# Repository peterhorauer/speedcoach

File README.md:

# speedcoach

A rowing speedcoach that measures speed and acceleration and displays them on a Graphic-LCD.

*Parts*

- Microcontroller STM32
- external memory
- GPS module
- Accelerometer
- Bluetooth module
- Graphic LCD
- Buttons

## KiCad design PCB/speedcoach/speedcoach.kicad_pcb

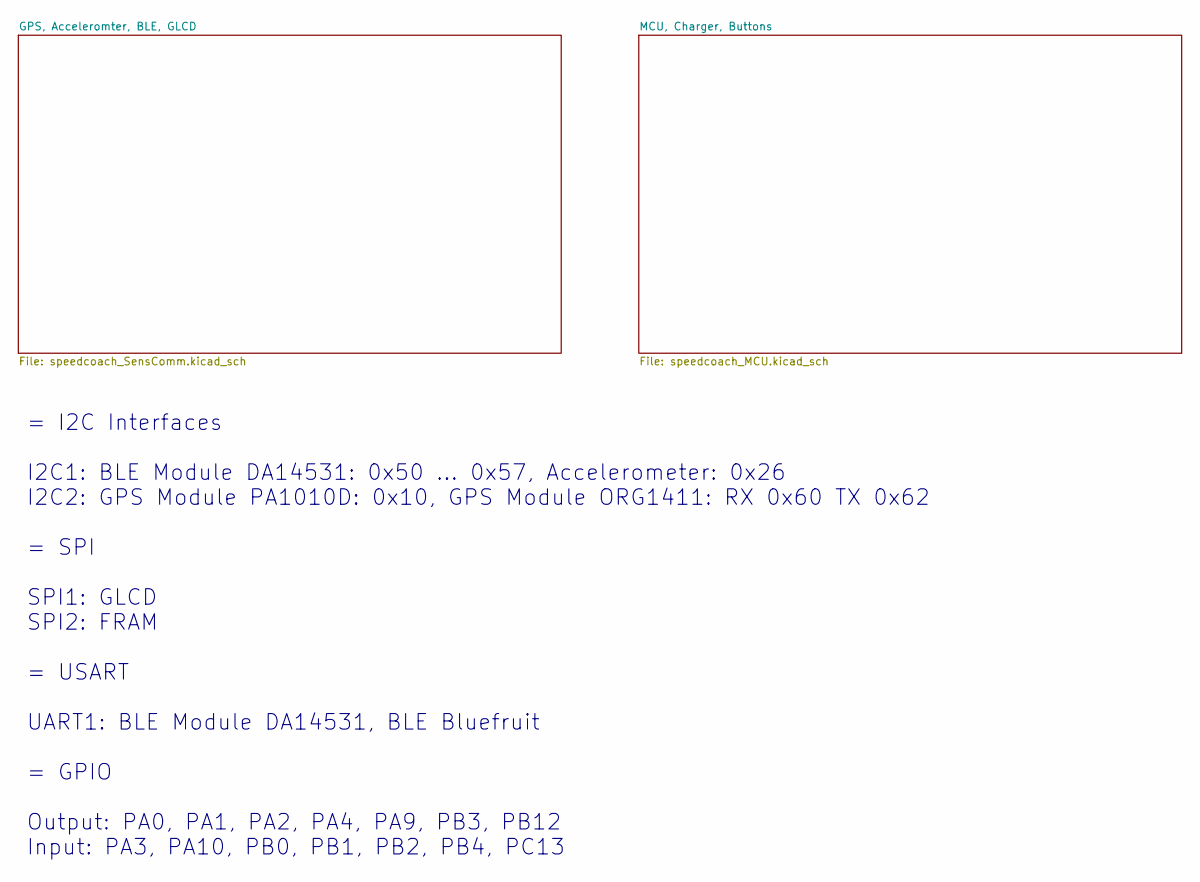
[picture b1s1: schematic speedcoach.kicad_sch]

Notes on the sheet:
= I2C Interfaces I2C1: BLE Module DA14531: 0x50 ... 0x57, Accelerometer: 0x26 I2C2: GPS Module PA1010D: 0x10, GPS Module ORG1411: RX 0x60 TX 0x62 = SPI SPI1: GLCD SPI2: FRAM = USART UART1: BLE Module DA14531, BLE Bluefruit = GPIO Output: PA0, PA1, PA2, PA4, PA9, PB3, PB12 Input: PA3, PA10, PB0, PB1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

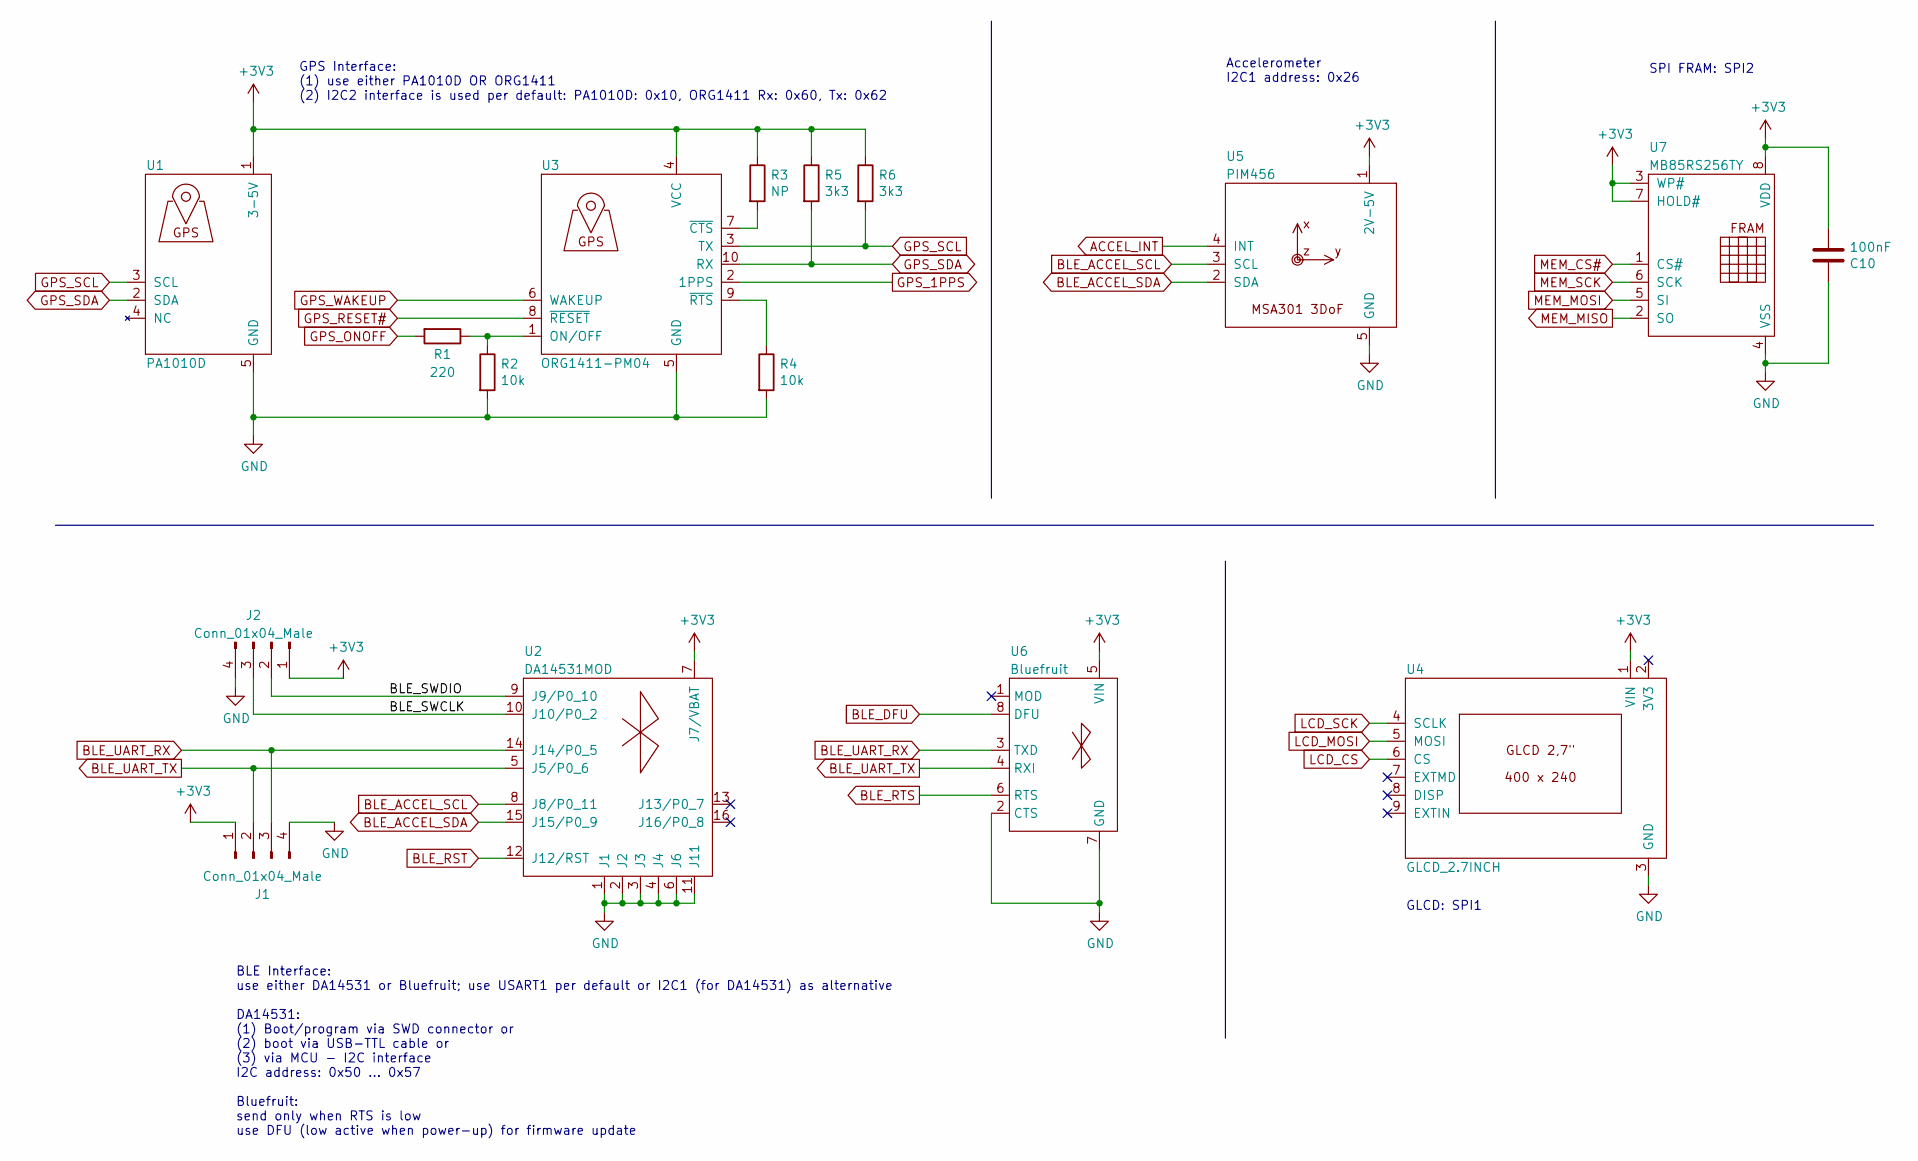
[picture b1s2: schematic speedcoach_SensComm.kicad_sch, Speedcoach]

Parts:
C10: 100nF; C_0805_2012Metric
J1, J2: Conn_01x04_Male; PinHeader_1x04_P2.54mm_Vertical
R1: 220; R_0805_2012Metric
R2, R4: 10k; R_0805_2012Metric
R3: NP; R_0805_2012Metric
R5, R6: 3k3; R_0805_2012Metric
U1: PA1010D; PA1010D_WH
U2: DA14531MOD; DA14531MOD-00F01002
U3: ORG1411-PM04; ORG1411
U4: GLCD_2.7INCH; SHARP_DISPLAY_400x240
U5: PIM456; PIM456_WH
U6: Bluefruit; Bluefruit_WH
U7: MB85RS256TY; SOP-8_3.9x4.9mm_P1.27mm

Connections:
+3V3: C10.1, J1.1, J2.1, R3.1, R5.1, R6.1, U1.1 (3-5V), U2.7 (J7/VBAT), U3.4 (VCC), U4.1 (VIN), U5.1 (2V-5V), U6.5 (VIN), U7.3 (WP#), U7.7 (HOLD#), U7.8 (VDD); also elsewhere on the board
/GPS, Acceleromter, BLE, GLCD/BLE_SWCLK: J2.3, U2.10 (J10/P0_2)
/GPS, Acceleromter, BLE, GLCD/BLE_SWDIO: J2.2, U2.9 (J9/P0_10)
ACCEL_INT: U5.4 (INT); also elsewhere on the board
BLE_ACCEL_SCL: U2.8 (J8/P0_11), U5.3 (SCL); also elsewhere on the board
BLE_ACCEL_SDA: U2.15 (J15/P0_9), U5.2 (SDA); also elsewhere on the board
BLE_DFU: U6.8 (DFU); also elsewhere on the board
BLE_RST: U2.12 (J12/RST); also elsewhere on the board
BLE_RTS: U6.6 (RTS); also elsewhere on the board
BLE_UART_RX: J1.3, U2.14 (J14/P0_5), U6.3 (TXD); also elsewhere on the board
BLE_UART_TX: J1.2, U2.5 (J5/P0_6), U6.4 (RXI); also elsewhere on the board
GND: C10.2, J1.4, J2.4, R2.2, R4.2, U1.5 (GND), U2.1 (J1), U2.2 (J2), U2.3 (J3), U2.4 (J4), U2.6 (J6), U2.11 (J11), U3.5 (GND), U4.3 (GND), U5.5 (GND), U6.2 (CTS), U6.7 (GND), U7.4 (VSS); also elsewhere on the board
GPS_1PPS: U3.2 (1PPS); also elsewhere on the board
GPS_ONOFF: R1.2; also elsewhere on the board
GPS_RESET#: U3.8 (~RESET); also elsewhere on the board
GPS_SCL: R6.2, U1.3 (SCL), U3.3 (TX); also elsewhere on the board
GPS_SDA: R5.2, U1.2 (SDA), U3.10 (RX); also elsewhere on the board
GPS_WAKEUP: U3.6 (WAKEUP); also elsewhere on the board
LCD_CS: U4.6 (CS); also elsewhere on the board
LCD_MOSI: U4.5 (MOSI); also elsewhere on the board
LCD_SCK: U4.4 (SCLK); also elsewhere on the board
MEM_CS#: U7.1 (CS#); also elsewhere on the board
MEM_MISO: U7.2 (SO); also elsewhere on the board
MEM_MOSI: U7.5 (SI); also elsewhere on the board
MEM_SCK: U7.6 (SCK); also elsewhere on the board
unnamed: R1.1, R2.1, U3.1 (ON/OFF)
unnamed: R3.2, U3.7 (~CTS)
unnamed: R4.1, U3.9 (~RTS)

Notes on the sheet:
Accelerometer I2C1 address: 0x26
SPI FRAM: SPI2
GLCD: SPI1
GPS Interface: (1) use either PA1010D OR ORG1411 (2) I2C2 interface is used per default: PA1010D: 0x10, ORG1411 Rx: 0x60, Tx: 0x62
BLE Interface: use either DA14531 or Bluefruit; use USART1 per default or I2C1 (for DA14531) as alternative DA14531: (1) Boot/program via SWD connector or (2) boot via USB-TTL cable or (3) via MCU - I2C interface I2C address: 0x50 ... 0x57 Bluefruit: send only when RTS is low use DFU (low active wh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

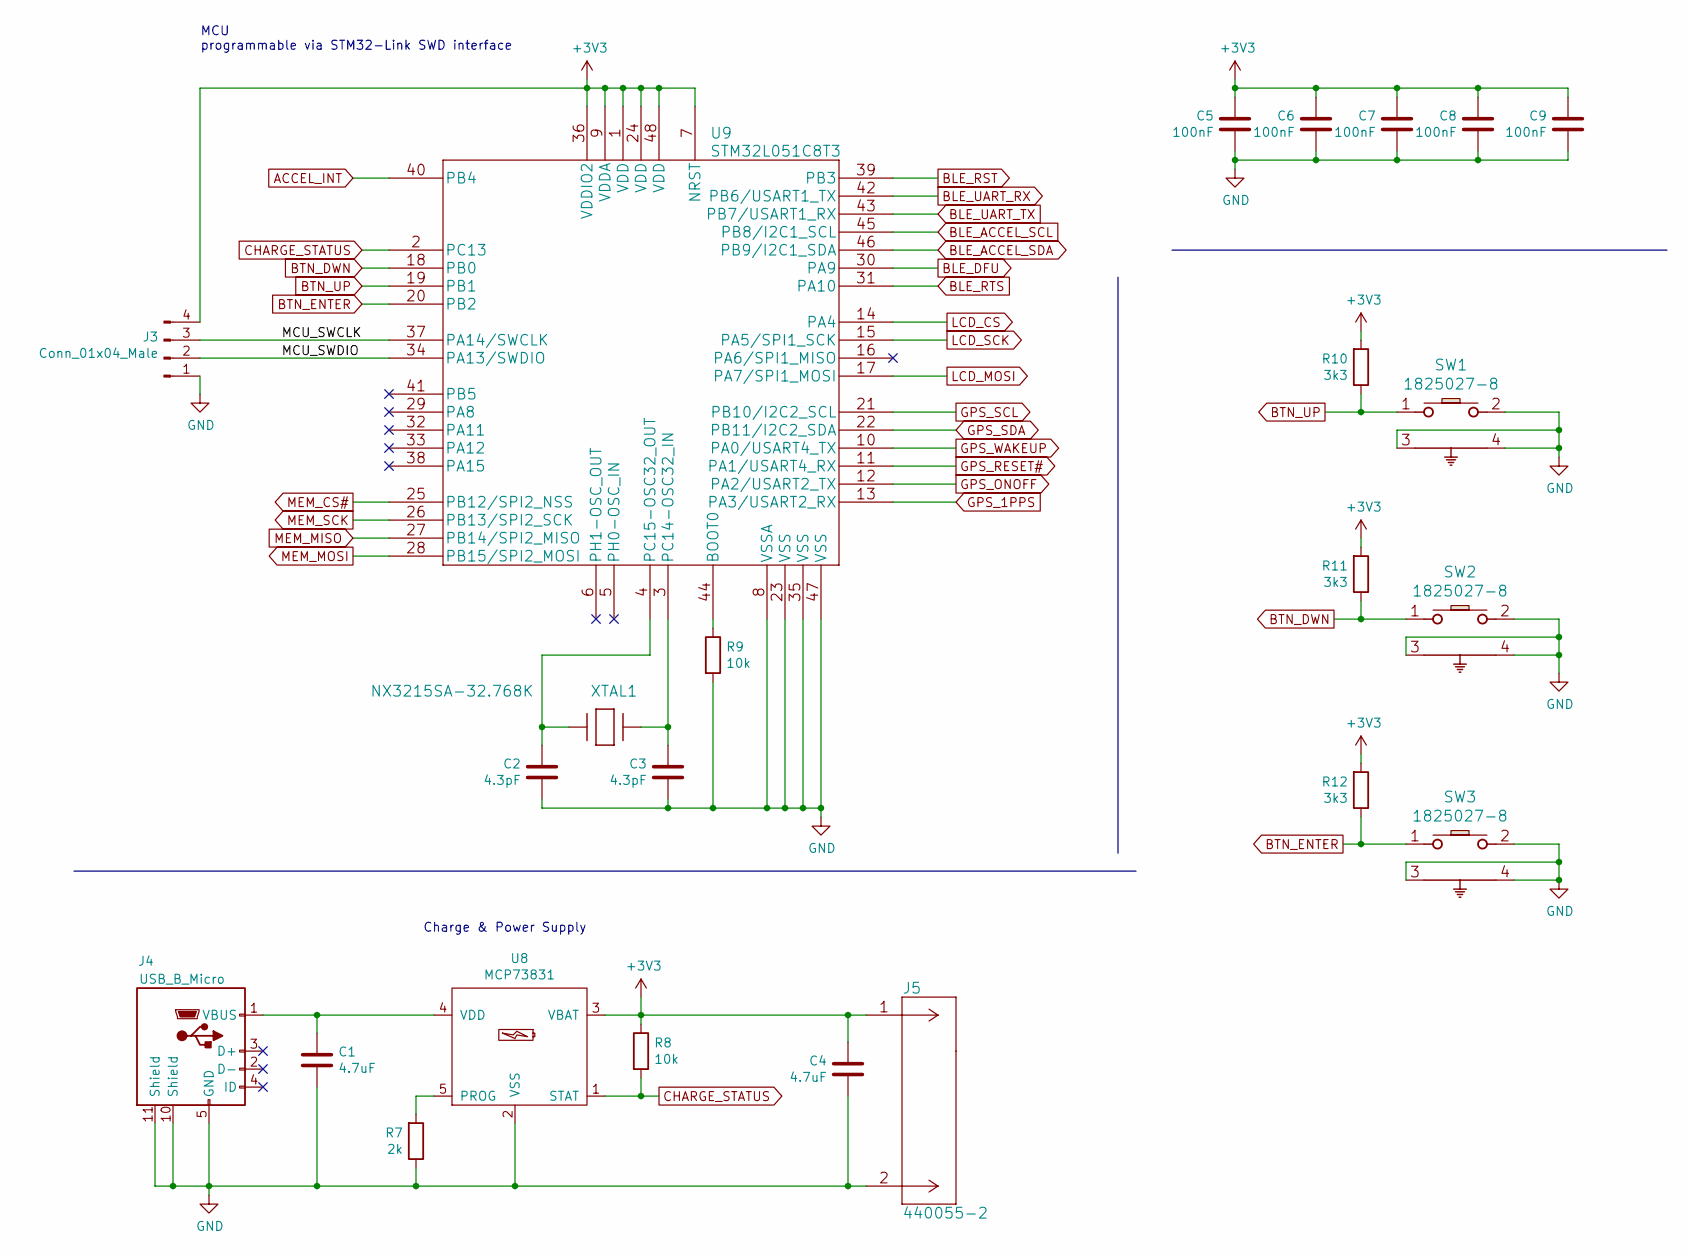
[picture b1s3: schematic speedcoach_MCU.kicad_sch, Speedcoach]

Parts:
C1, C4: 4.7uF; C_0805_2012Metric
C2, C3: 4.3pF; C_0805_2012Metric
C5, C6, C7, C8, C9: 100nF; C_0805_2012Metric
J3: Conn_01x04_Male; PinHeader_1x04_P2.54mm_Vertical
J4: USB_B_Micro; 10118194-0001LF
J5: 440055-2
R7: 2k; R_0805_2012Metric
R8, R9: 10k; R_0805_2012Metric
R10, R11, R12: 3k3; R_0805_2012Metric
SW1, SW2, SW3: 1825027-8
U8: MCP73831; MCP73831T-2ATIOT
U9: STM32L051C8T3; LQFP-48_7x7mm_P0.5mm
XTAL1: NX3215SA-32.768K; NX3215SA-32.768K-EXS00A-MU00003

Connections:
+3V3: C4.2, C5.2, C6.2, C7.2, C8.2, C9.2, J3.4, J5.1, R8.1, R10.2, R11.2, R12.2, U8.3 (VBAT), U9.1 (VDD), U9.7 (NRST), U9.9 (VDDA), U9.24 (VDD), U9.36 (VDDIO2), U9.48 (VDD); also elsewhere on the board
/MCU, Charger, Buttons/MCU_SWCLK: J3.3, U9.37 (PA14/SWCLK)
/MCU, Charger, Buttons/MCU_SWDIO: J3.2, U9.34 (PA13/SWDIO)
ACCEL_INT: U9.40 (PB4); also elsewhere on the board
BLE_ACCEL_SCL: U9.45 (PB8/I2C1_SCL); also elsewhere on the board
BLE_ACCEL_SDA: U9.46 (PB9/I2C1_SDA); also elsewhere on the board
BLE_DFU: U9.30 (PA9); also elsewhere on the board
BLE_RST: U9.39 (PB3); also elsewhere on the board
BLE_RTS: U9.31 (PA10); also elsewhere on the board
BLE_UART_RX: U9.42 (PB6/USART1_TX); also elsewhere on the board
BLE_UART_TX: U9.43 (PB7/USART1_RX); also elsewhere on the board
BTN_DWN: R11.1, SW2.1, U9.18 (PB0)
BTN_ENTER: R12.1, SW3.1, U9.20 (PB2)
BTN_UP: R10.1, SW1.1, U9.19 (PB1)
CHARGE_STATUS: R8.2, U8.1 (STAT), U9.2 (PC13)
GND: C1.2, C2.1, C3.1, C4.1, C5.1, C6.1, C7.1, C8.1, C9.1, J3.1, J4.5 (GND), J4.10 (Shield), J4.11 (Shield), J5.2, R7.1, R9.2, SW1.2, SW1.3, SW1.4, SW2.2, SW2.3, SW2.4, SW3.2, SW3.3, SW3.4, U8.2 (VSS), U9.8 (VSSA), U9.23 (VSS), U9.35 (VSS), U9.47 (VSS); also elsewhere on the board
GPS_1PPS: U9.13 (PA3/USART2_RX); also elsewhere on the board
GPS_ONOFF: U9.12 (PA2/USART2_TX); also elsewhere on the board
GPS_RESET#: U9.11 (PA1/USART4_RX); also elsewhere on the board
GPS_SCL: U9.21 (PB10/I2C2_SCL); also elsewhere on the board
GPS_SDA: U9.22 (PB11/I2C2_SDA); also elsewhere on the board
GPS_WAKEUP: U9.10 (PA0/USART4_TX); also elsewhere on the board
LCD_CS: U9.14 (PA4); also elsewhere on the board
LCD_MOSI: U9.17 (PA7/SPI1_MOSI); also elsewhere on the board
LCD_SCK: U9.15 (PA5/SPI1_SCK); also elsewhere on the board
MEM_CS#: U9.25 (PB12/SPI2_NSS); also elsewhere on the board
MEM_MISO: U9.27 (PB14/SPI2_MISO); also elsewhere on the board
MEM_MOSI: U9.28 (PB15/SPI2_MOSI); also elsewhere on the board
MEM_SCK: U9.26 (PB13/SPI2_SCK); also elsewhere on the board
unnamed: C1.1, J4.1 (VBUS), U8.4 (VDD)
unnamed: C2.2, U9.4 (PC15-OSC32_OUT), XTAL1.1
unnamed: C3.2, U9.3 (PC14-OSC32_IN), XTAL1.2
unnamed: R7.2, U8.5 (PROG)
unnamed: R9.1, U9.44 (BOOT0)

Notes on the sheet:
Charge & Power Supply
MCU programmable via STM32-Link SWD interface

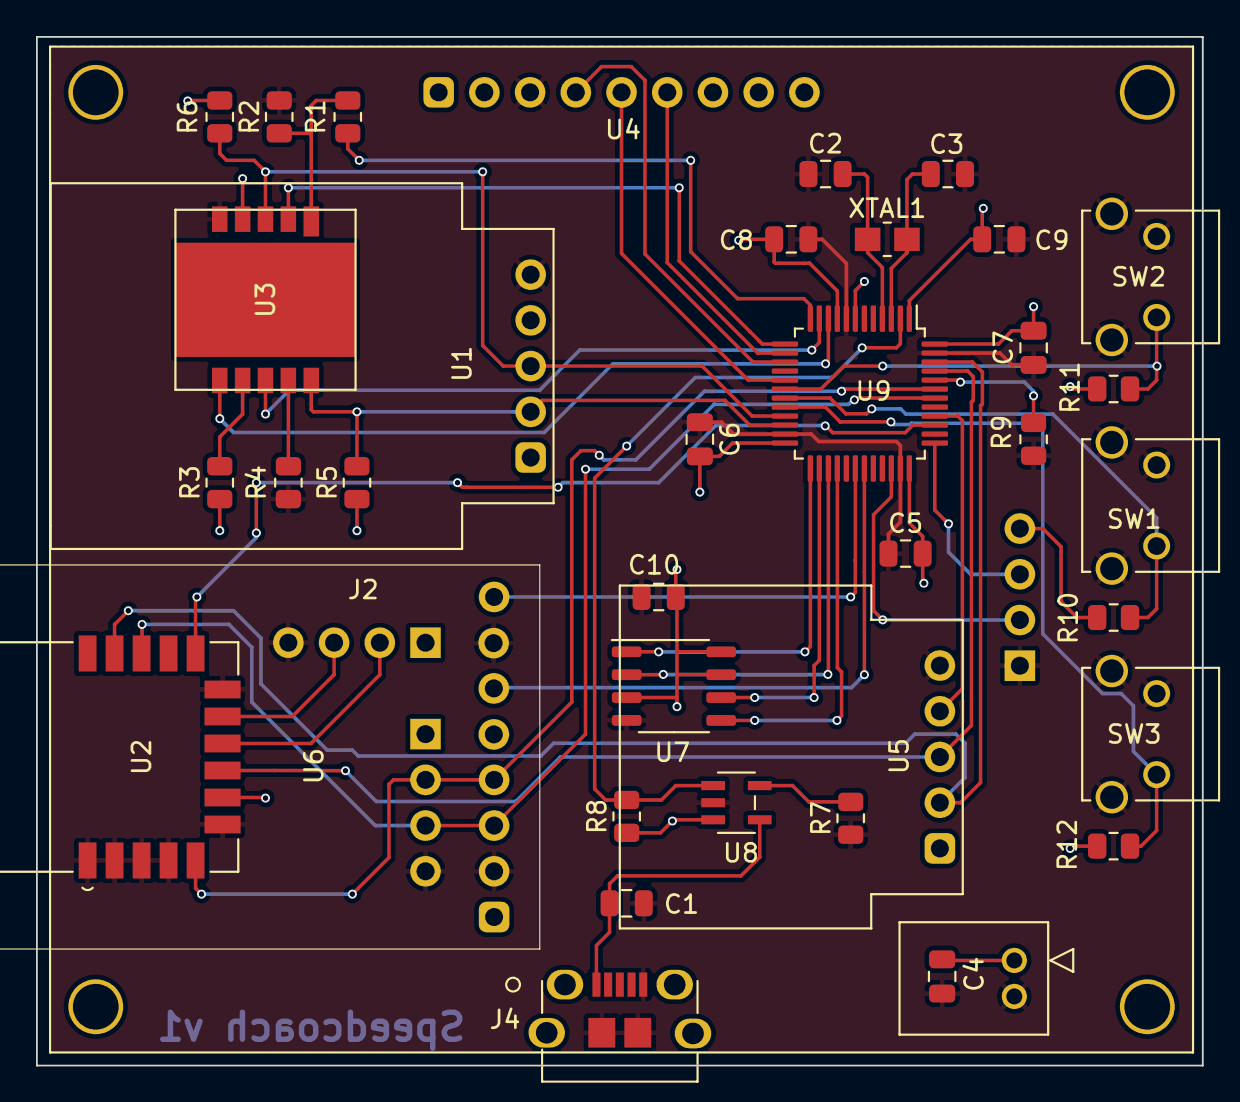
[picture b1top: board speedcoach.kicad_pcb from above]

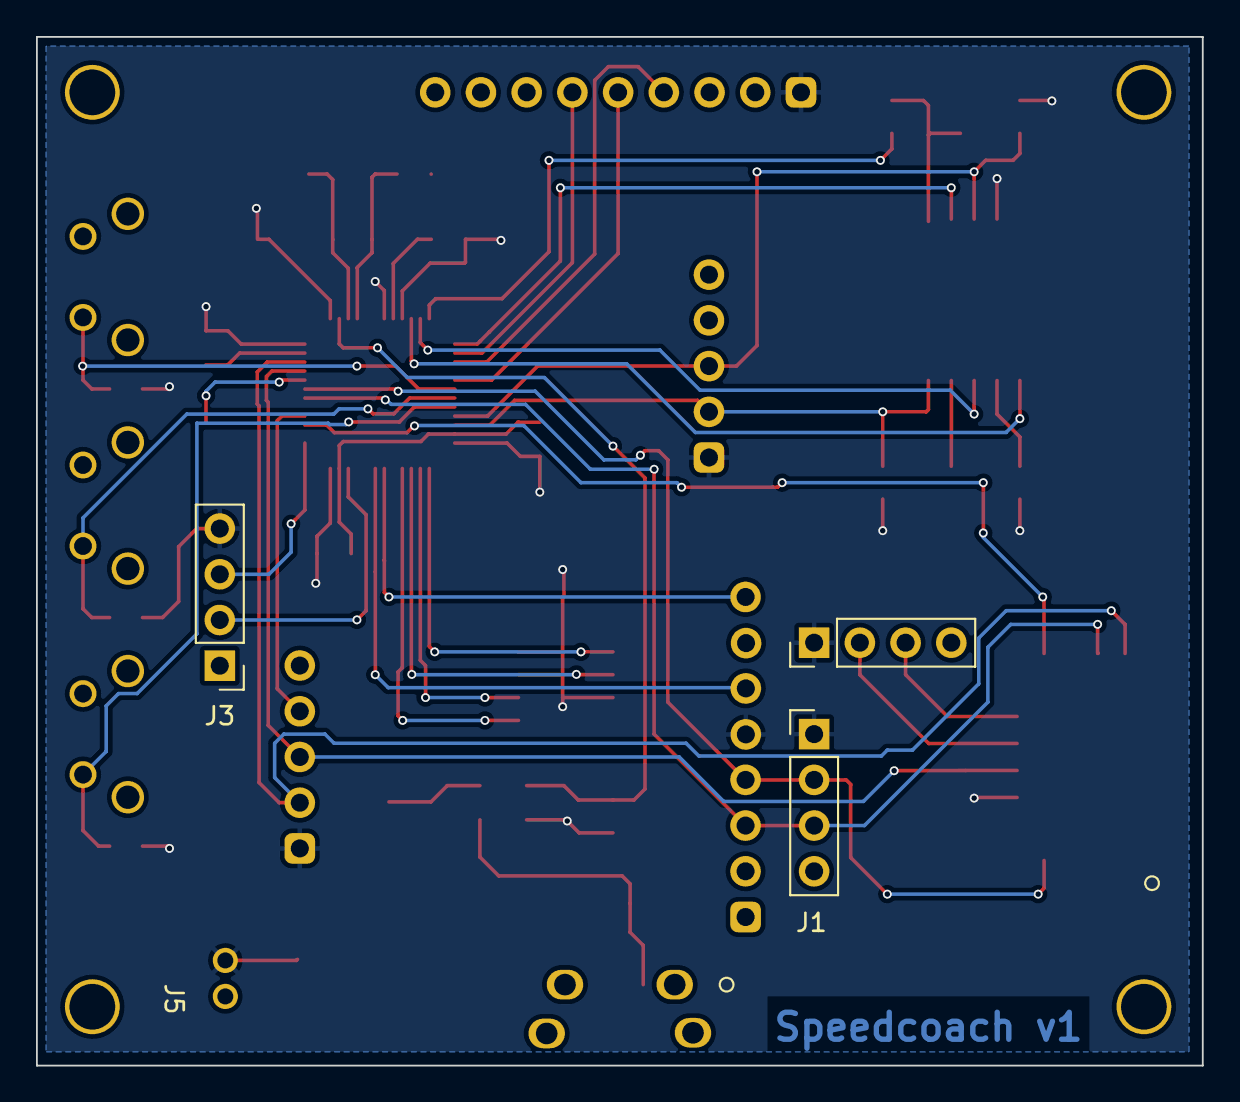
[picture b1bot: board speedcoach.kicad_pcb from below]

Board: 2 copper layers, 64.8 x 57.1 mm, 40 parts (3 on the bottom side), 39 nets.

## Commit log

2022-02-03 selected parts
2022-02-04 schematic work in progress
2022-02-15 added Bluefruit module
2022-02-15 revised MCU
2022-02-16 updated some labels, finetuning
2022-02-16 placement
2022-02-17 routed v1
2022-02-20 added 3D models
2022-02-20 added image
2022-02-21 optimization
2022-02-21 added PDFs

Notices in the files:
parts and their libraries:
Copyright 2021 Accelerated Designs. All rights reserved.
